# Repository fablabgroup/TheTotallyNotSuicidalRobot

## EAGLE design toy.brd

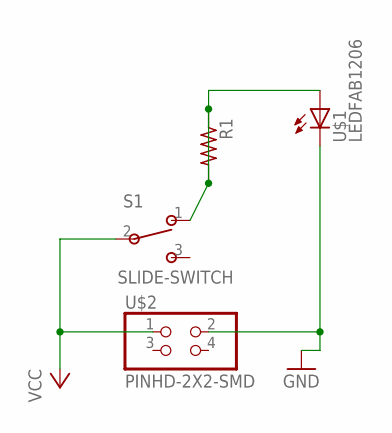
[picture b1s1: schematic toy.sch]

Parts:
R1: RES-US1206FAB; R1206FAB
S1: SLIDE-SWITCH; AYZ0102AGRLC
U$1: LEDFAB1206; LED1206FAB
U$2: PINHD-2X2-SMD; 2X02SMD

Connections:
GND: U$1.2 (C), U$2.2
unnamed: R1.1, R1.2, S1.1, U$1.1 (A)
VCC: S1.2, U$2.1

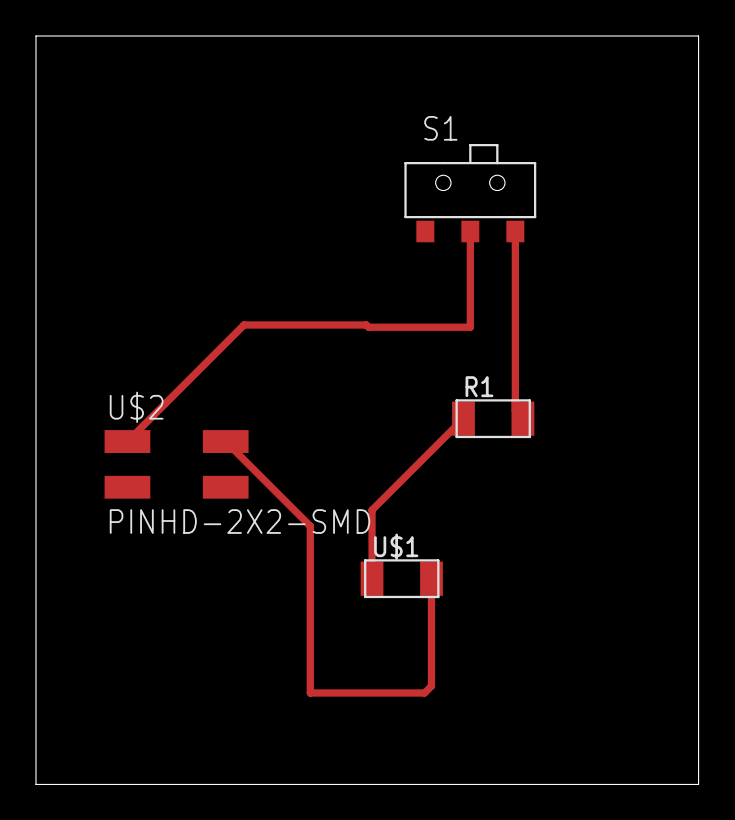
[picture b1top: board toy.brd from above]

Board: 2 copper layers, 36.8 x 41.6 mm, 4 parts (0 on the bottom side), 3 nets.

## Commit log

2019-03-15 Create ProjectDescription
2019-03-25 Add files via upload
    quick sketch
2019-03-26 Add files via upload
    initial code
2019-04-02 reset button removed
2019-04-14 second us sensor
2019-04-17 speed control
2019-04-23 different vars to different sensors
